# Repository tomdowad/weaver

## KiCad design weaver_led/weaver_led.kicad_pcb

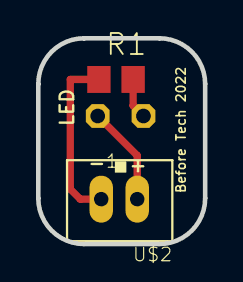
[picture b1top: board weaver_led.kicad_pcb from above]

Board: 2 copper layers, 9.3 x 11.4 mm, 3 parts (1 on the bottom side), 3 nets.

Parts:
LED1: LED5MM
R1: R0805
U$2: JST-PH_2-PIN_HEADER; JST_B2B-PH_HEADER

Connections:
unnamed: LED1.K, R1.2
unnamed: R1.1, U$2.P1
unnamed: LED1.A, U$2.P2

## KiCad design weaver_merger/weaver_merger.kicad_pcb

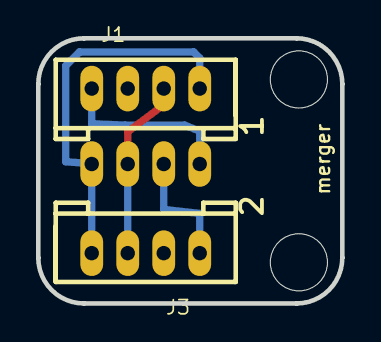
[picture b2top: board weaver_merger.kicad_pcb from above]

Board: 2 copper layers, 16.9 x 14.7 mm, 5 parts (1 on the bottom side), 4 nets.

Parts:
@HOLE0, @HOLE1: (no value)
J1, J2, J3: 4P-2.0; HW4-2.0

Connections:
GND: J1.4, J2.4, J3.4
unnamed: J1.1, J2.1
unnamed: J2.2, J3.1
unnamed: J1.3, J2.3, J3.3

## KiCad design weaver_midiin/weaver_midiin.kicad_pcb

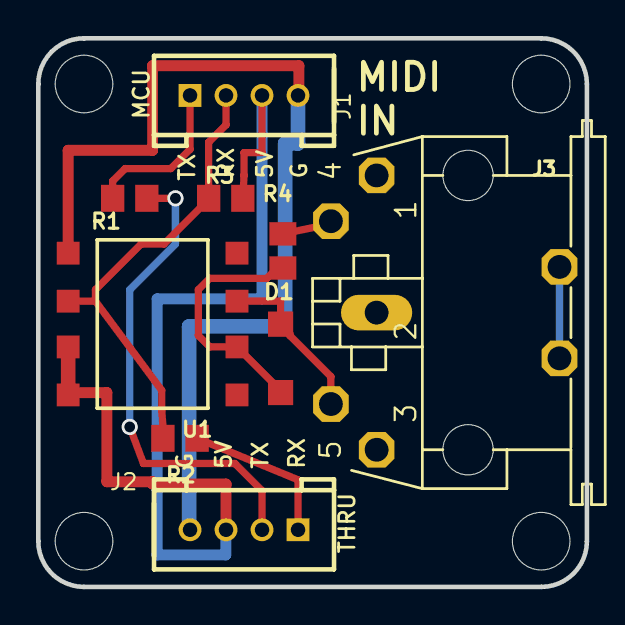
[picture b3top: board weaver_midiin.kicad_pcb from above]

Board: 2 copper layers, 30.5 x 30.5 mm, 13 parts (0 on the bottom side), 10 nets.

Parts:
@HOLE0, @HOLE1, @HOLE2, @HOLE3: (no value)
D1: 1N4148SOD-123; SOD123
J1, J2: 4P-2.0; HW4-2.0
J3: MAB5SH
R1, R2, R4: 220R; R0805
R3: 470R; R0805
U1: 6N137S; SO8-GW300

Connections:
+5V: J1.3, J2.3, R3.2, U1.7, U1.8
GND: J1.4, J2.4, U1.5
unnamed: D1.C, R4.1, U1.2
unnamed: J3.4, R4.2
unnamed: J2.2, R1.2
unnamed: D1.A, J3.5, U1.3
unnamed: J2.1, R2.2
PE: J3.PE, J3.PE@
RX: J1.1, R1.1
TX: J1.2, R2.1, R3.1, U1.6
